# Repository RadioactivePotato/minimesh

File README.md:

# minimesh
A tiny, low-power Meshtastic compatible device with GPS, enviroment sensor and an OLED display powered by nRF52840

# About

I made this because I found that alot of pre-made Meshtastic nodes are too big and too power hungry, this node uses the nRF52840 chip instead of the ESP32-S3 since it's much more power efficient, while only sacrificing the Wi-Fi feature.

# Images

<details>
<summary>Schematic (click to expand)</summary>

| Schematic |
|-----------|
|  |

</details>

| PCB | 3D Preview | Case |
|-----|------------|------|
|  |  |  |
|  |  |  |

# BOM

| Qty | Item                            | Notes                         | Cost (USD) | URL |
|-----|---------------------------------|-------------------------------|------------|-----|
| 2   | nRF52840 ProMicro               | MCU (incl vat+shipping)       | 8.16       | [AliExpress](https://www.aliexpress.com/item/1005006446457448.html)                         |
| 2   | HT-RA62 Transceiver Module      | Can be replaced with RA-01SH  | 15.63      | [AliExpress](https://www.aliexpress.com/item/1005005543917617.html)                         |
| 2   | 0.96" OLED Display              | Pinout needs to be GND,VCC... | 4.36       | [AliExpress](https://www.aliexpress.com/item/1005008738379315.html)                         |
| 4   | Switches                        |                               | 0.99       | [AliExpress](https://www.aliexpress.com/item/4001125532910.html)                            |
| 2   | GP-02-KIT GPS Module            |                               | 11.44      | [AliExpress](https://www.aliexpress.com/item/1005008346885630.html)                         |
| 2   | Slide Switch                    | For GPS module (5mm)          | 1.64       | [AliExpress](https://www.aliexpress.com/item/1005007162182882.html)                         |
| 2   | 868MHz antenna (SMA M)          |                               | 12.60      | [AliExpress](https://www.aliexpress.com/item/1005006712636707.html)                         |
| 2   | BME280 Module                   | Telementary data              | 5.96       | [AliExpress](https://www.aliexpress.com/item/1005008511564094.html)                         |
| 2   | 3.7V BMS Board                  | Prevent overcharging/discharging | 1.32    | [AliExpress](https://www.aliexpress.com/item/1005008760086623.html)                         |
| 2   | Battery Connector               |                               | 0.67       | [AliExpress](https://www.aliexpress.com/item/1005002564191148.html)                         |
|-----|---------------------------------|-------------------------------|------------|-----|
| 5   | PCB                             | Min order qty - 5             | 1.50       | JLCPCB                                                                                      |
|-----|---------------------------------|-------------------------------|------------|-----|
|-----|---------------------------------|-------------------------------| 64.29USD   |-----|

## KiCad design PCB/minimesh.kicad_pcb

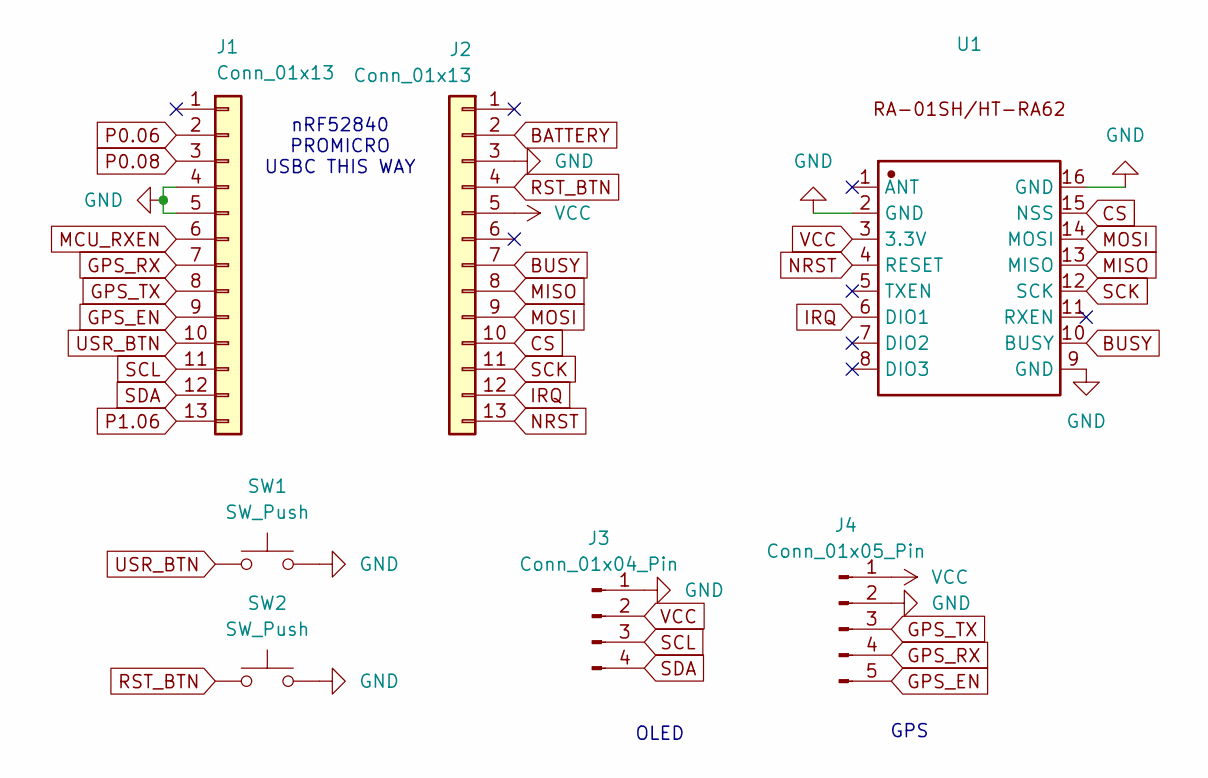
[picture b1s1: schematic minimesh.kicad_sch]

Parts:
J1, J2: Conn_01x13; PinHeader_1x13_P2.54mm_Vertical
J3: Conn_01x04_Pin; PinHeader_1x04_P2.54mm_Vertical
J4: Conn_01x05_Pin; PinHeader_1x05_P2.54mm_Vertical
SW1, SW2: SW_Push; SW_SPST_B3U-1000P
U1: RA-01SH

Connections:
BATTERY: J2.2
BUSY: J2.7, U1.10 (BUSY)
CS: J2.10, U1.15 (NSS)
GND: J1.4, J1.5, J2.3, J3.1, J4.2, SW1.2, SW2.2, U1.2 (GND), U1.9 (GND), U1.16 (GND)
GPS_EN: J1.9, J4.5
GPS_RX: J1.7, J4.4
GPS_TX: J1.8, J4.3
IRQ: J2.12, U1.6 (DIO1)
MCU_RXEN: J1.6
MISO: J2.8, U1.13 (MISO)
MOSI: J2.9, U1.14 (MOSI)
NRST: J2.13, U1.4 (RESET)
P0.06: J1.2
P0.08: J1.3
P1.06: J1.13
RST_BTN: J2.4, SW2.1
SCK: J2.11, U1.12 (SCK)
SCL: J1.11, J3.3
SDA: J1.12, J3.4
USR_BTN: J1.10, SW1.1
VCC: J2.5, J3.2, J4.1, U1.3 (3.3V)

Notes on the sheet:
OLED
GPS
nRF52840 PROMICRO USBC THIS WAY

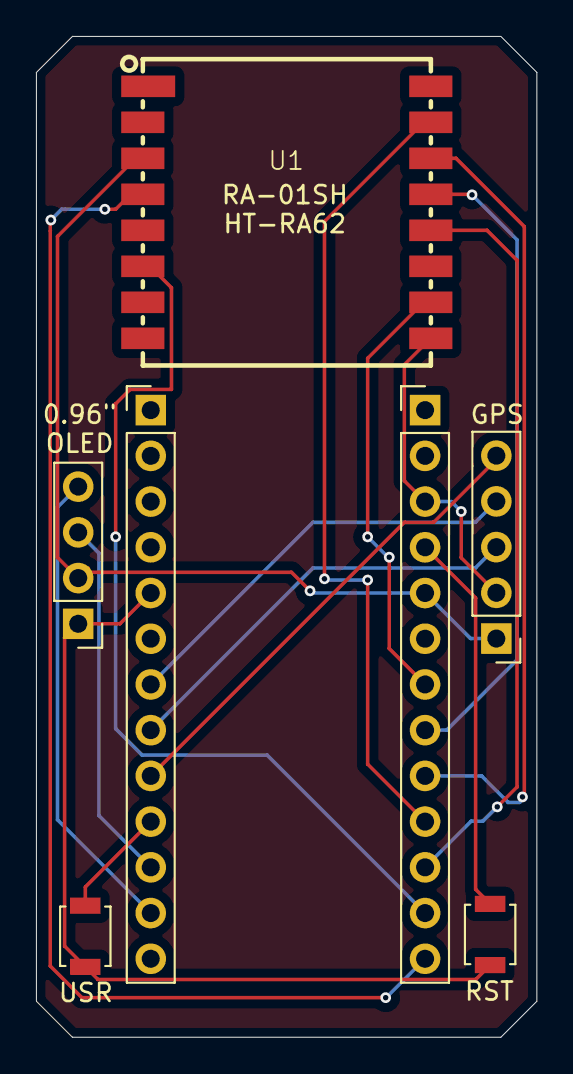
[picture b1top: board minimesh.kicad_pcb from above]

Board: 2 copper layers, 27.8 x 55.6 mm, 7 parts (0 on the bottom side), 16 nets.

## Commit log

2025-07-12 july 12
2025-07-12 bom update
2025-07-13 july 13
2025-07-13 updated bom
2025-07-13 updated promicro source for a cheaper price
2025-07-16 july 16 case design
2025-07-16 repo setup
2025-07-16 changed bom to 2 units since a mesh is 2+ nodes
2025-07-16 added more images
2025-07-19 total cost update
